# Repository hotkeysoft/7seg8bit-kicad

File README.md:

# Four-digit seven-segment indicator for 8 bit values
### Rev C August 2019
  - Reverse input protection
  - Real decimal mode w/four digits
  - Configurable modes via jumpers:
    - Decimal / HEX mode
      - Signed Decimal (-256-255)
      - Unsigned Decimal (0-255)
      - Hexadecimal (0-FF)
    - Latch mode
      - Latch value on L->H transition
      - Latch value on H->L transition
      - Unlatched (live display)  

*Note: This revision was produced and works*

### Rev B August 2019
  - Added programming header
  - Removed dim mode

*Note: Never produced*

### Rev A July 2019
- ATmega328P microcontroller running at 8MHz (internal clock)
- 2 digit 7-segment display
- Configurable modes via solder jumper:
  - HEX mode (default)
    - 00-FF
  - Pseudo-decimal
    - 00-99, .00-.99, ..00-..55 (dot = 100)
- Unlatched (live display)

Images
============
|Front                                                 | Back                                              |
|------------------------------------------------------|---------------------------------------------------|
|||

### Schematics (pdf)
- [Complete schematics](./img/schema.pdf)

### PCB Images (svg)
- [Top](./img/pcb-front.svg)
- [Bottom](./img/pcb-back.svg)

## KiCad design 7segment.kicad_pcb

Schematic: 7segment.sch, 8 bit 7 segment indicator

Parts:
C1, C2, C3: 0.1uF; C_0805_2012Metric_Pad1.15x1.40mm_HandSolder
D1: MBR0520LT; D_SOD-123
J1: VCC; PinHeader_1x01_P2.54mm_Vertical
J2: IN_UP; PinHeader_1x08_P2.54mm_Vertical
J3: GND; PinHeader_1x01_P2.54mm_Vertical
J4: IN_DOWN; PinHeader_1x08_P2.54mm_Vertical
J5: RESET; PinHeader_1x01_P2.54mm_Vertical
J6, J7: LATCH; PinHeader_1x01_P2.54mm_Vertical
JP1: BIN/DEC; PinHeader_1x03_P2.54mm_Vertical
JP2: LATCH MODE; PinHeader_1x03_P2.54mm_Vertical
R3: 4.7k; R_0805_2012Metric_Pad1.15x1.40mm_HandSolder
RN1, RN2: 330; R_Array_Convex_4x0603
RN3: 10K; R_Array_Convex_4x0603
U1, U3: LTD-2601G
U2: ATmega328P-AU; TQFP-32_7x7mm_P0.8mm

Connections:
/IN0: J2.1, J4.1, U2.12 (PB0)
/IN1: J2.2, J4.2, U2.13 (PB1)
/IN2: J2.3, J4.3, U2.14 (PB2)
/IN6: J2.7, J4.7, U2.7 (XTAL1/PB6)
/IN7: J2.8, J4.8, U2.8 (XTAL2/PB7)
/VIN: D1.2, J1.1
D0: U1.9, U2.23 (PC0)
D1: U1.6, U2.24 (PC1)
D2: U2.25 (PC2), U3.9
D3: U2.26 (PC3), U3.6
GND: C1.2, C2.2, C3.1, J3.1, JP1.3, JP2.3, RN3.6, RN3.8, U2.3 (GND), U2.5 (GND), U2.21 (GND)
MISO: J2.5, J4.5, U2.16 (PB4)
MOSI: J2.4, J4.4, U2.15 (PB3)
unnamed: C3.2, U2.20 (AREF)
unnamed: J6.1, J7.1, U2.27 (PC4)
unnamed: RN1.1, U2.30 (PD0)
unnamed: RN1.2, U2.31 (PD1)
unnamed: RN1.3, U2.32 (PD2)
unnamed: RN1.4, U2.1 (PD3)
unnamed: RN2.5, U2.11 (PD7)
unnamed: RN2.6, U2.10 (PD6)
unnamed: RN2.7, U2.9 (PD5)
unnamed: RN2.8, U2.2 (PD4)
SCK: J2.6, J4.6, U2.17 (PB5)
SEG_A: RN1.8, U1.7, U3.7
SEG_B: RN1.7, U1.8, U3.8
SEG_C: RN1.6, U1.3, U3.3
SEG_D: RN1.5, U1.2, U3.2
SEG_DP: RN2.4, U1.5, U3.5
SEG_E: RN2.1, U1.1, U3.1
SEG_F: RN2.2, U1.10, U3.10
SEG_G: RN2.3, U1.4, U3.4
SEL_LATCHMODE: JP2.2, RN3.1, RN3.2, U2.22 (ADC7)
SEL_NUMBERBASE: JP1.2, RN3.3, RN3.4, U2.19 (ADC6)
VCC: C1.1, C2.1, D1.1, JP1.1, JP2.1, R3.1, RN3.5, RN3.7, U2.4 (VCC), U2.6 (VCC), U2.18 (AVCC)
~RESET: J5.1, R3.2, U2.29 (~RESET~/PC6)

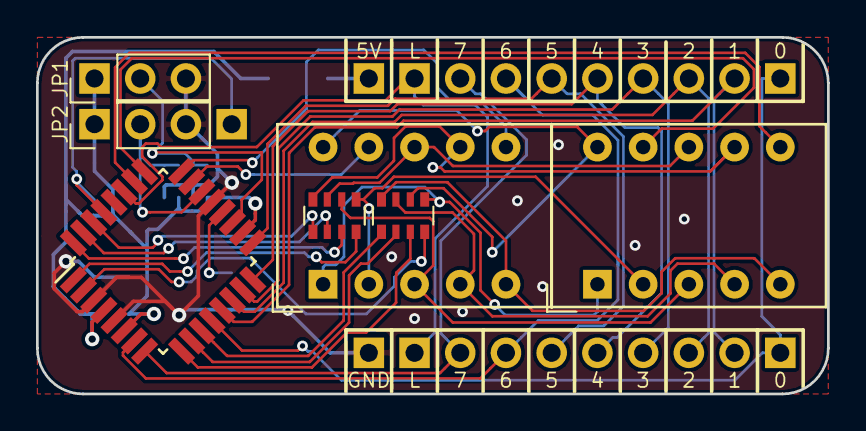
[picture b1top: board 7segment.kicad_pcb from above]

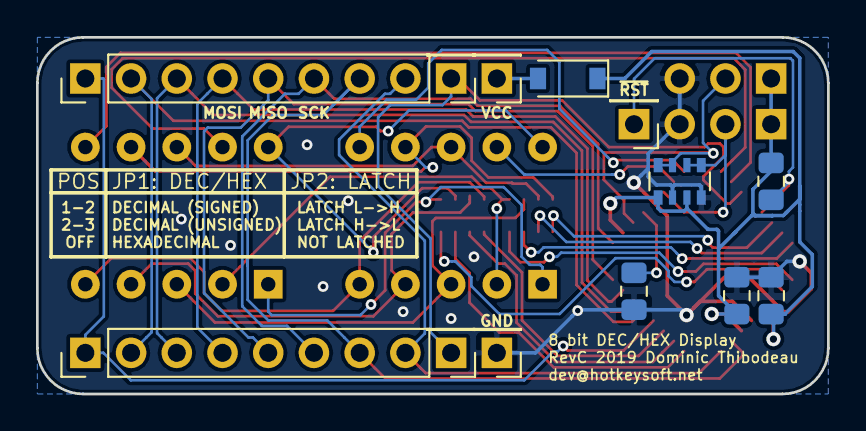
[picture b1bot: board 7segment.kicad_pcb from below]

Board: 2 copper layers, 43.9 x 19.8 mm, 20 parts (13 on the bottom side), 36 nets.

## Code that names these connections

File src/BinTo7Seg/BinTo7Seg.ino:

/* Binary to 7 Segment display (8 bits)
 * Rev C 
 * 2019-08-17 Dominic Thibodeau
 * 
 * Modes: Hex / Signed Decimal / Unsigned Decimal
 *        Latched / Live
 *        
 * Target: ATmega328p
 */

/*
 * IN0-IN7: PB0-PB7
 * 
 * D0: PC0
 * D1: PC1
 * D2: PC2
 * D3: PC3
 * 
 * IN_LATCH: PC4
 * IN_DEBUG: PC5
 * 
 * SEGA-SEGDP: PD0-PD7
 * 
 * SEL_NUMBERBASE: ADC6
 * SEL_LATCHMODE: ADC7
 */

#define PA 0
#define PB 1
#define PC 2
#define PD 3

#define SEL_D0 14
#define SEL_D1 15
#define SEL_D2 16
#define SEL_D3 17

#define IN_LATCH 18

#define SEL_NUMBERBASE A6
#define SEL_LATCHMODE A7

const int digitDelay = 2;

bool triggeredOnce = false;
int lastLatchPinState;
byte latchedInput = 0;

enum DIGIT {
  DIGIT_D0 = SEL_D0,
  DIGIT_D1 = SEL_D1,
  DIGIT_D2 = SEL_D2,
  DIGIT_D3 = SEL_D3,
};

enum LATCHMODE {
  LATCH_LH,
  LATCH_HL,
  LATCH_LIVE
};

enum NUMBERBASE {
  NB_SIGNED_DEC,
  NB_UNSIGNED_DEC,
  NB_HEX
};

LATCHMODE getLatchMode() {
  int value = analogRead(SEL_LATCHMODE);
  if (value < 300)
    return LATCH_LH;
  else if (value > 700)
    return LATCH_HL;
  else 
    return LATCH_LIVE;  
}

NUMBERBASE getNumberBase() {
  int value = analogRead(SEL_NUMBERBASE);
  if (value < 300)
    return NB_SIGNED_DEC;
  else if (value > 700)
    return NB_UNSIGNED_DEC;
  else 
    return NB_HEX;      
}

void setup() {
  // Segments
  portMode(PD, OUTPUT);
  // Inputs
  portMode(PB, INPUT);

  pinMode(SEL_D0, OUTPUT);
  pinMode(SEL_D1, OUTPUT);
  pinMode(SEL_D2, OUTPUT);
  pinMode(SEL_D3, OUTPUT);

  pinMode(IN_LATCH, INPUT_PULLUP); //TODODT: remove pullup in prod  
  lastLatchPinState = digitalRead(IN_LATCH);
}

const PROGMEM byte digits[17] = {
  0b00111111, // 0
  0b00000110, // 1
  0b01011011, // 2  
  0b01001111, // 3
  0b01100110, // 4
  0b01101101, // 5
  0b01111101, // 6
  0b00000111, // 7 
  0b01111111, // 8
  0b01101111, // 9 
  0b01110111, // A
  0b01111100, // b
  0b00111001, // C
  0b01011110, // d
  0b01111001, // E
  0b01110001, // F
  0b01000000  // -
};

void outputBlank(DIGIT pos) {
  clearDigits();
  portWrite(PD, 255);
  selectDigit(pos);
}

void outputMinus(DIGIT pos) {
  clearDigits();
  portWrite(PD, ~pgm_read_byte_near(digits + 16));
  selectDigit(pos);  
}

void outputDigit(const byte digit, DIGIT pos) {
  clearDigits();
  if (digit > 15) return;
  portWrite(PD, ~pgm_read_byte_near(digits + digit));
  selectDigit(pos);    
}

void clearDigits() {
  digitalWrite(SEL_D0, LOW);
  digitalWrite(SEL_D1, LOW);
  digitalWrite(SEL_D2, LOW);
  digitalWrite(SEL_D3, LOW);
}

void selectDigit(DIGIT digit) {
  digitalWrite(digit, HIGH);
}

void outputNumberHex(const uint8_t number) {
  outputBlank(DIGIT_D0);
  delay(digitDelay);

  outputBlank(DIGIT_D1);
  delay(digitDelay);
  
  outputDigit(number >> 4, DIGIT_D2);
  delay(digitDelay);

  outputDigit(number&0x0F, DIGIT_D3);
  delay(digitDelay);
}

void outputNumberUnsignedDecimal(uint8_t number) {
  if (number > 99) {
    outputDigit(number/100, DIGIT_D1);
  } else {
    outputBlank(DIGIT_D1);
  }
  delay(digitDelay);  

  if (number > 9) {
    outputDigit((number/10)%10, DIGIT_D2);
  } else {
    outputBlank(DIGIT_D2);    
  }
  delay(digitDelay);
  
  outputDigit(number%10, DIGIT_D3);
  delay(digitDelay);
}

void outputNumberSignedDecimal(uint8_t number) {
  if (number > 127) {
    uint8_t unsignedValue = -number;

    outputNumberUnsignedDecimal(unsignedValue);  

    if (unsignedValue > 99)
      outputMinus(DIGIT_D0);
    else if (unsignedValue > 9)
      outputMinus(DIGIT_D1);
    else 
      outputMinus(DIGIT_D2);

    delay(digitDelay);
  } else {
    outputNumberUnsignedDecimal(number);
  }
}

void outputNumber(uint8_t number) {
    switch(getNumberBase()) {
      case NB_SIGNED_DEC:
        outputNumberSignedDecimal(number);
        break;
      case NB_UNSIGNED_DEC:
        outputNumberUnsignedDecimal(number);
        break;
      default:
        outputNumberHex(number);
    }
}

void loop() { 
  clearDigits();
  
  LATCHMODE latchMode = getLatchMode();

  if (latchMode != LATCH_LIVE) {
    bool triggered = false;
    int currLatchState = digitalRead(IN_LATCH);
    triggered = ((latchMode == LATCH_LH) && !lastLatchPinState && currLatchState) || 
      ((latchMode == LATCH_HL) && lastLatchPinState && !currLatchState);
    lastLatchPinState = currLatchState;

    if (triggered) {
      triggeredOnce = true;
      latchedInput = portRead(PB);
    }
    if (triggeredOnce) {
      outputNumber(latchedInput);
    }
  } else {   
    outputNumber(portRead(PB));
  }
}

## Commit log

2019-07-22 Initial import
2019-08-10 Work on RevB
2019-08-16 Added source code
2020-07-28 Cleanup, added images
2020-07-28 Create LICENSE
2020-07-28 Add commonlib submodule
2020-07-28 Revision B
2020-07-28 Rev C
